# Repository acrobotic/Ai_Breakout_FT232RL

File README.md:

Overview
---
This repository includes the Eagle design files (schematics and layout) for our [FT232RL Brekout Board][1]. The FT232RL is a 
popular Integrated Circuit (IC) that provides a single-chip USB to asynchronous serial data (UART) transfer interface. This IC is
commonly known as the **FTDI chip** as it's manufactured by Future Technology Devices Internationa (FTDI).  

The FT232RL is extremely useful for sending data back and forth between a PC and a microcontroller (such as the ATMega328p 
that's used in the Arduino Uno R3). It can even be used to program a microcontroller whose boot section has been pre-loaded
with a bootloader (e.g., Optiboot).

For more info on how to use the FTDI and its use for data communication and microcontroller programming, please visit:
[http://learn.acrobotic.com/FTDI][2]

Product page
---
Please consider buying products from Acrobotic to help fund future Open-Source projects like this! We'll always put our best effort in every project, and release all our design files and code for you to use.

[Tutorials, technical details, and more information about this product can be found here: http://acrobotic.com/catalog/product/view/id/31][1]

License Information
---

All contents of this repository are licensed under a [Creative Commons Attribution-ShareAlike 3.0 Unported License](http://creativecommons.org/licenses/by-sa/3.0/).

[1]: http://acrobotic.com/catalog/product/view/id/31 "FT232RL Breakout Board"
[2]: http://learn.acrobotic.com/FTDI "Acrobotic FTDI Tutorial"

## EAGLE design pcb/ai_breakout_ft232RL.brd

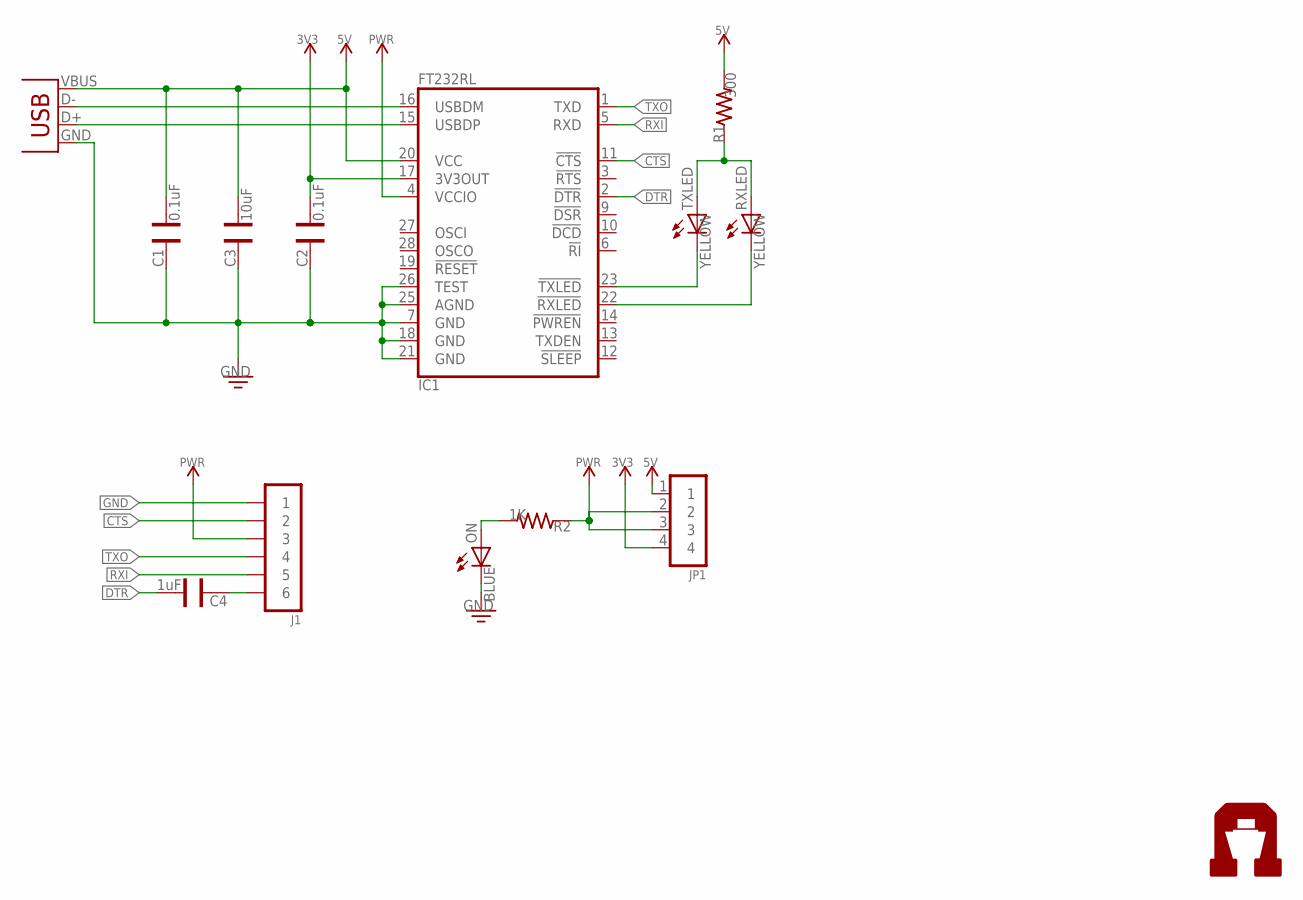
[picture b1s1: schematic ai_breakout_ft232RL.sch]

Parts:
C1, C2: 0.1uF; CAP-0603
C3: 10uF; CAP-0603
C4: 1uF; CAP-0603
IC1: FT2332RL; SSOP28-LD
J1: 1X06LONG; 1X06-LONG
JP1: 1X04NOSILK; 1X04-NOSILK
ON: BLUE; LED-0603
R1: 300; RES-0603
R2: 1K; RES-0603
RXLED: YELLOW; LED-0603
TXLED: YELLOW; LED-0603
U$3: AI-LOGOL; AI-LOGO-L
USB1: USBMICROB-TH; USB-MICROB-TH

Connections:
3V3: C2.1, IC1.17 (3V3OUT), JP1.4
5V: C1.1, C3.1, IC1.20 (VCC), JP1.1, R1.2, USB1.VBUS
CTS: IC1.11 (!CTS), J1.2
DTR: C4.1, IC1.2 (!DTR)
GND: C1.2, C2.2, C3.2, IC1.7 (GND), IC1.18 (GND), IC1.21 (GND), IC1.25 (AGND), IC1.26 (TEST), J1.1, ON.C, USB1.GND
unnamed: IC1.23 (!TXLED), TXLED.C
unnamed: IC1.22 (!RXLED), RXLED.C
unnamed: IC1.16 (USBDM), USB1.D-
unnamed: IC1.15 (USBDP), USB1.D+
unnamed: ON.A, R2.2
unnamed: R1.1, RXLED.A, TXLED.A
unnamed: C4.2, J1.6
PWR: IC1.4 (VCCIO), J1.3, JP1.2, JP1.3, R2.1
RXI: IC1.5 (RXD), J1.5
TXO: IC1.1 (TXD), J1.4

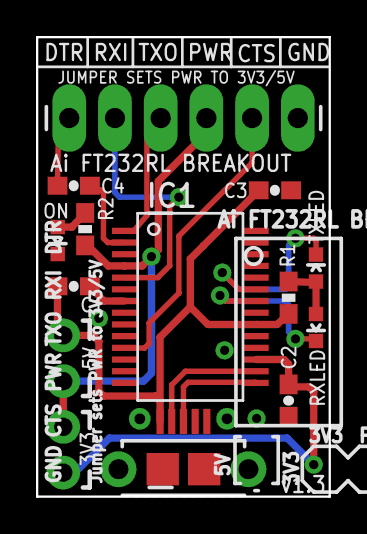
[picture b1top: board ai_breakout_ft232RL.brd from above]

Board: 2 copper layers, 16.3 x 25.5 mm, 14 parts (1 on the bottom side), 15 nets.

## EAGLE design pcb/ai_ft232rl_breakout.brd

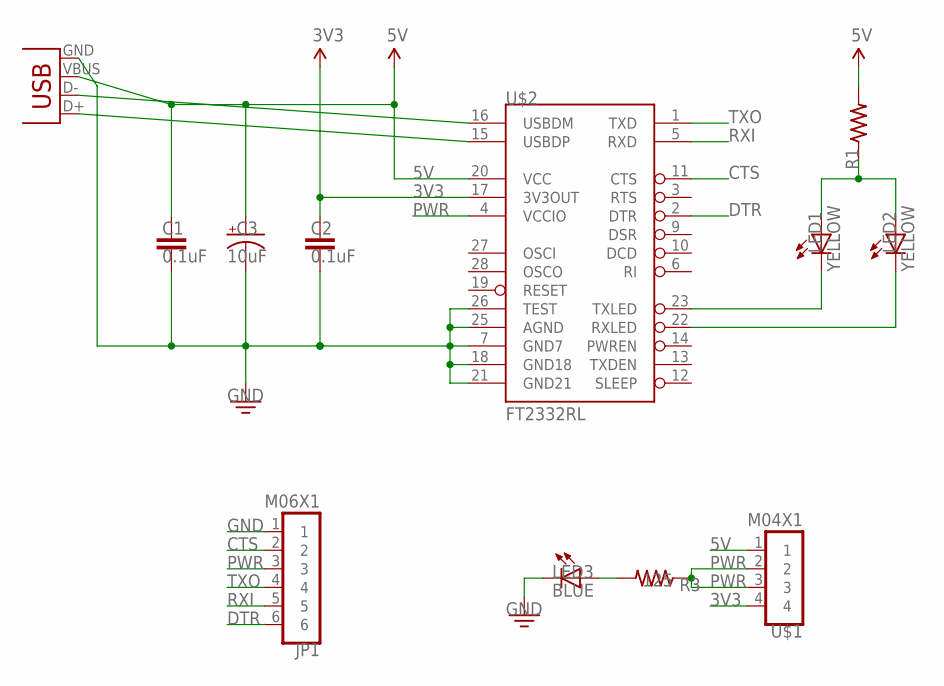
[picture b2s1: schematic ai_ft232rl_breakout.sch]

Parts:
C1, C2: 0.1uF; 0603-CAP
C3: 10uF; EIA3216
JP1: M06X1; 1X06-LONG
LED1, LED2: YELLOW; LED-0603
LED3: BLUE; LED-0603
R1: RES; 0603-RES
R3: 125; 0603-RES
U$1: M04X1; 1X04
U$2: FT2332RL; SSOP28-LD
USB1: USB-MICROB

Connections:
3V3: C2.1, U$1.4, U$2.17 (3V3OUT)
5V: C1.1, C3.A (+), R1.2, U$1.1, U$2.20 (VCC), USB1.VBUS
CTS: JP1.2, U$2.11 (CTS)
DTR: JP1.6, U$2.2 (DTR)
GND: C1.2, C2.2, C3.C (-), JP1.1, LED3.C, U$2.7 (GND7), U$2.18 (GND18), U$2.21 (GND21), U$2.25 (AGND), U$2.26 (TEST), USB1.GND
unnamed: LED1.C, U$2.23 (TXLED)
unnamed: LED2.C, U$2.22 (RXLED)
unnamed: U$2.16 (USBDM), USB1.D-
unnamed: U$2.15 (USBDP), USB1.D+
unnamed: LED1.A, LED2.A, R1.1
unnamed: LED3.A, R3.2
PWR: JP1.3, R3.1, U$1.2, U$1.3, U$2.4 (VCCIO)
RXI: JP1.5, U$2.5 (RXD)
TXO: JP1.4, U$2.1 (TXD)

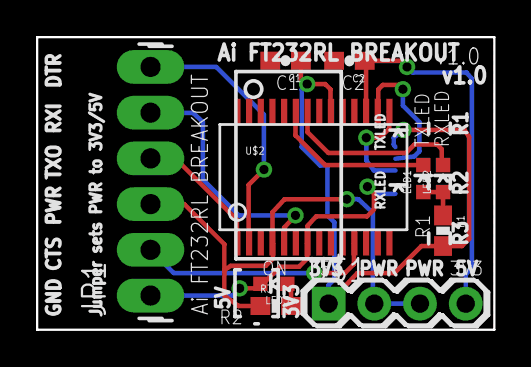
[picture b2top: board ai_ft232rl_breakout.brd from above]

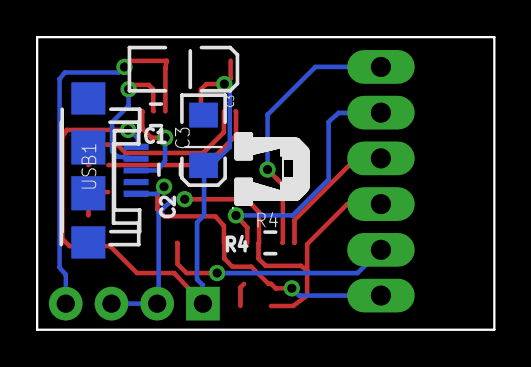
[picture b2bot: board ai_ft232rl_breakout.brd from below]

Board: 2 copper layers, 25.4 x 16.3 mm, 12 parts (2 on the bottom side), 14 nets.

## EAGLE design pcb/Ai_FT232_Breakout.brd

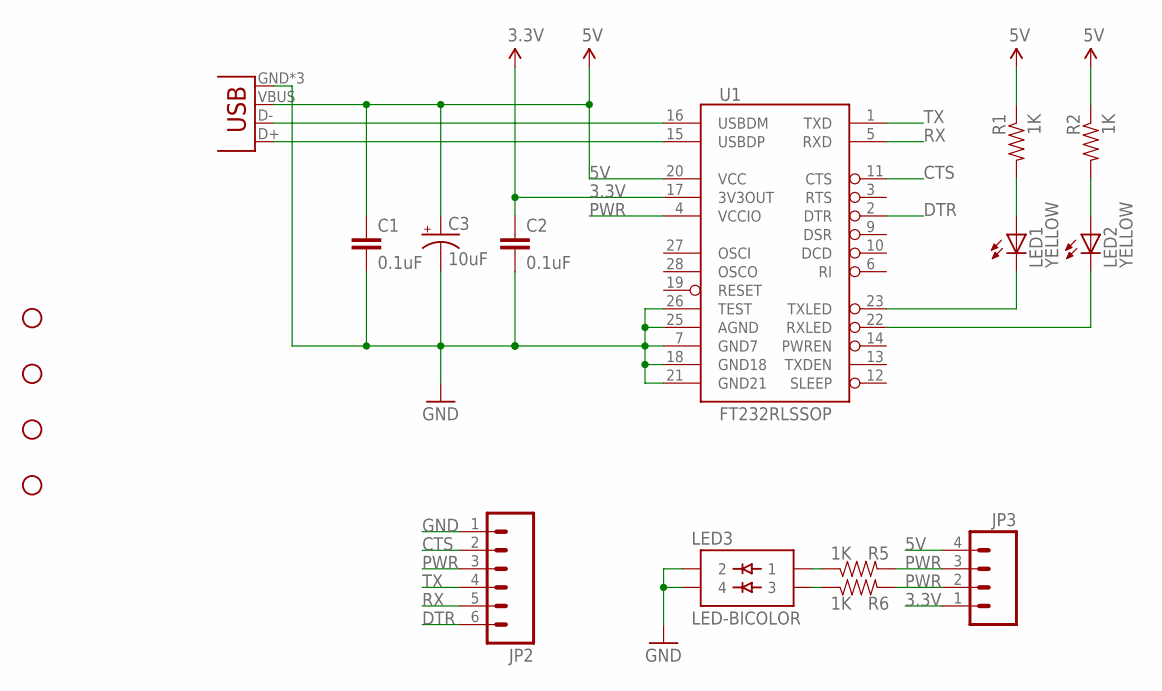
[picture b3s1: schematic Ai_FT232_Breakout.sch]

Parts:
C1, C2: 0.1uF; 0805
C3: 10uF; EIA3216-KIT
JP2: M06LONGPADS; 1X06_LONGPADS
JP3: M04PTH; 1X04
LED1, LED2: YELLOW; LED-0603
LED3: LED-BICOLOR; LED-BICOLOR-SMD
R1, R2, R5, R6: 1K; 0805
STANDOFF1, STANDOFF2, STANDOFF3, STANDOFF4: STAND-OFF
U1: FT232RLSSOP; SSOP28DB
USB: USB-MICROB

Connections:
3.3V: C2.1, JP3.1, U1.17 (3V3OUT)
5V: C1.1, C3.A (+), JP3.4, R1.1, R2.1, U1.20 (VCC), USB.VBUS
CTS: JP2.2, U1.11 (CTS)
DTR: JP2.6, U1.2 (DTR)
GND: C1.2, C2.2, C3.C (-), JP2.1, LED3.2 (4), LED3.3 (2), U1.7 (GND7), U1.18 (GND18), U1.21 (GND21), U1.25 (AGND), U1.26 (TEST), USB.GND, USB.MT1 (GND), USB.MT2 (GND)
unnamed: LED1.C, U1.23 (TXLED)
unnamed: LED2.C, U1.22 (RXLED)
unnamed: U1.16 (USBDM), USB.D-
unnamed: U1.15 (USBDP), USB.D+
unnamed: LED2.A, R2.2
unnamed: LED1.A, R1.2
unnamed: LED3.1, R5.1
unnamed: JP3.3, R5.2
unnamed: LED3.4 (3), R6.1
PWR: JP2.3, JP3.2, R6.2, U1.4 (VCCIO)
RX: JP2.5, U1.5 (RXD)
TX: JP2.4, U1.1 (TXD)

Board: 2 copper layers, 18 parts (0 on the bottom side), 17 nets, no tracks yet.

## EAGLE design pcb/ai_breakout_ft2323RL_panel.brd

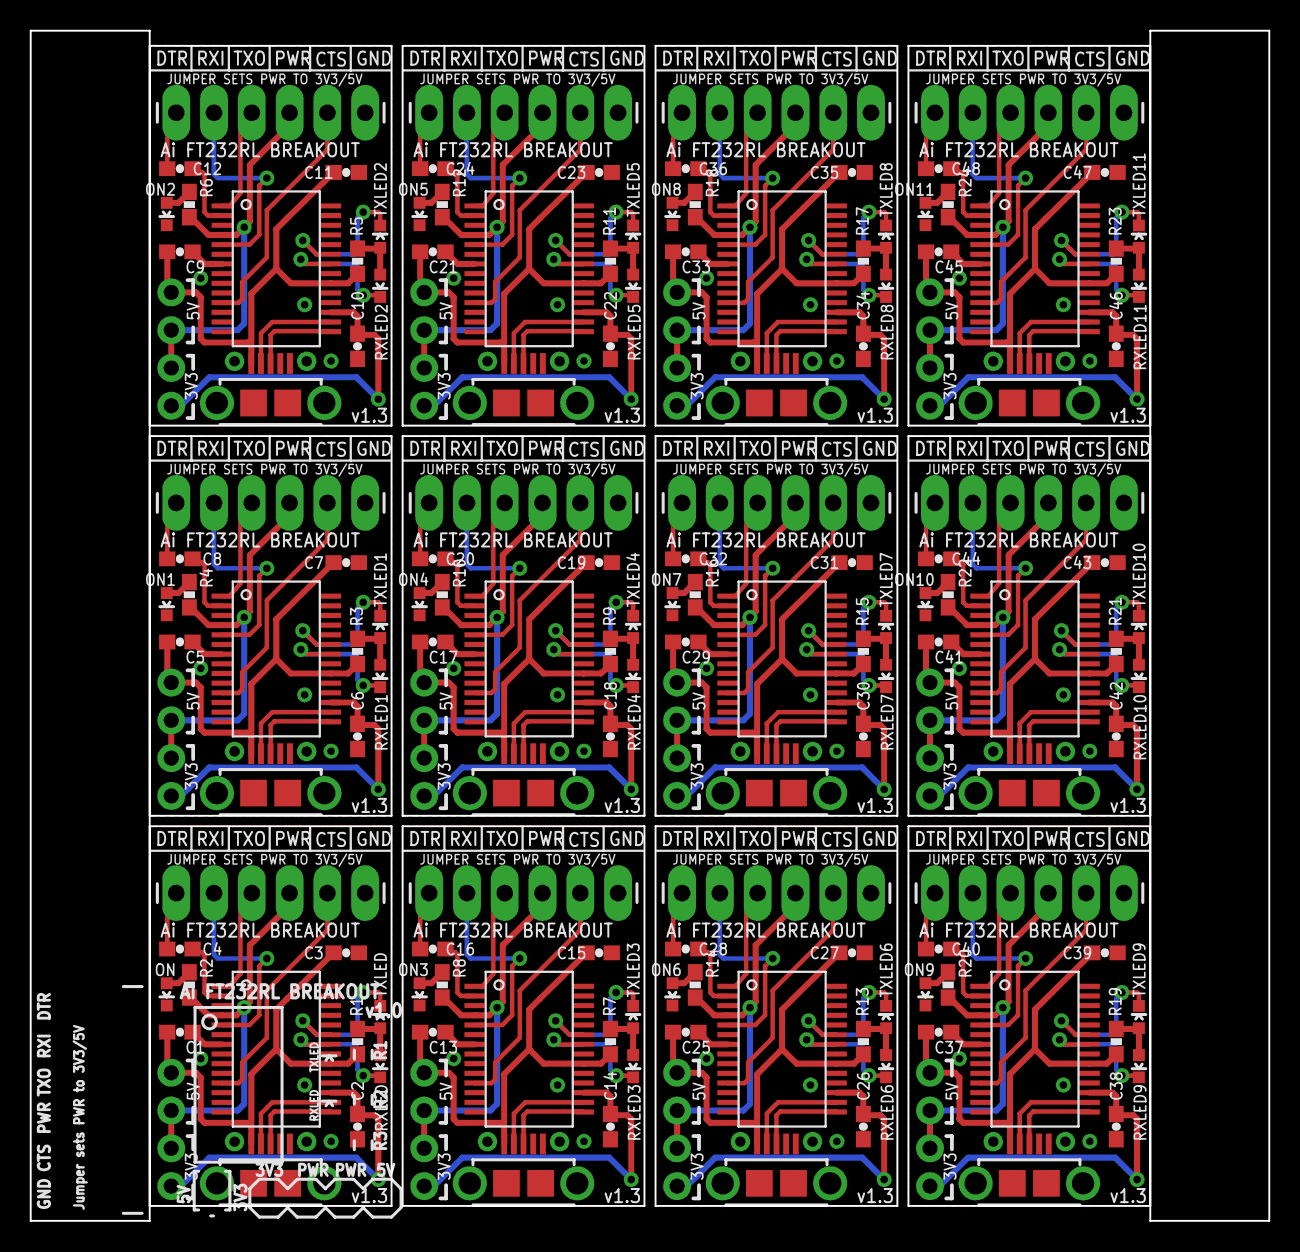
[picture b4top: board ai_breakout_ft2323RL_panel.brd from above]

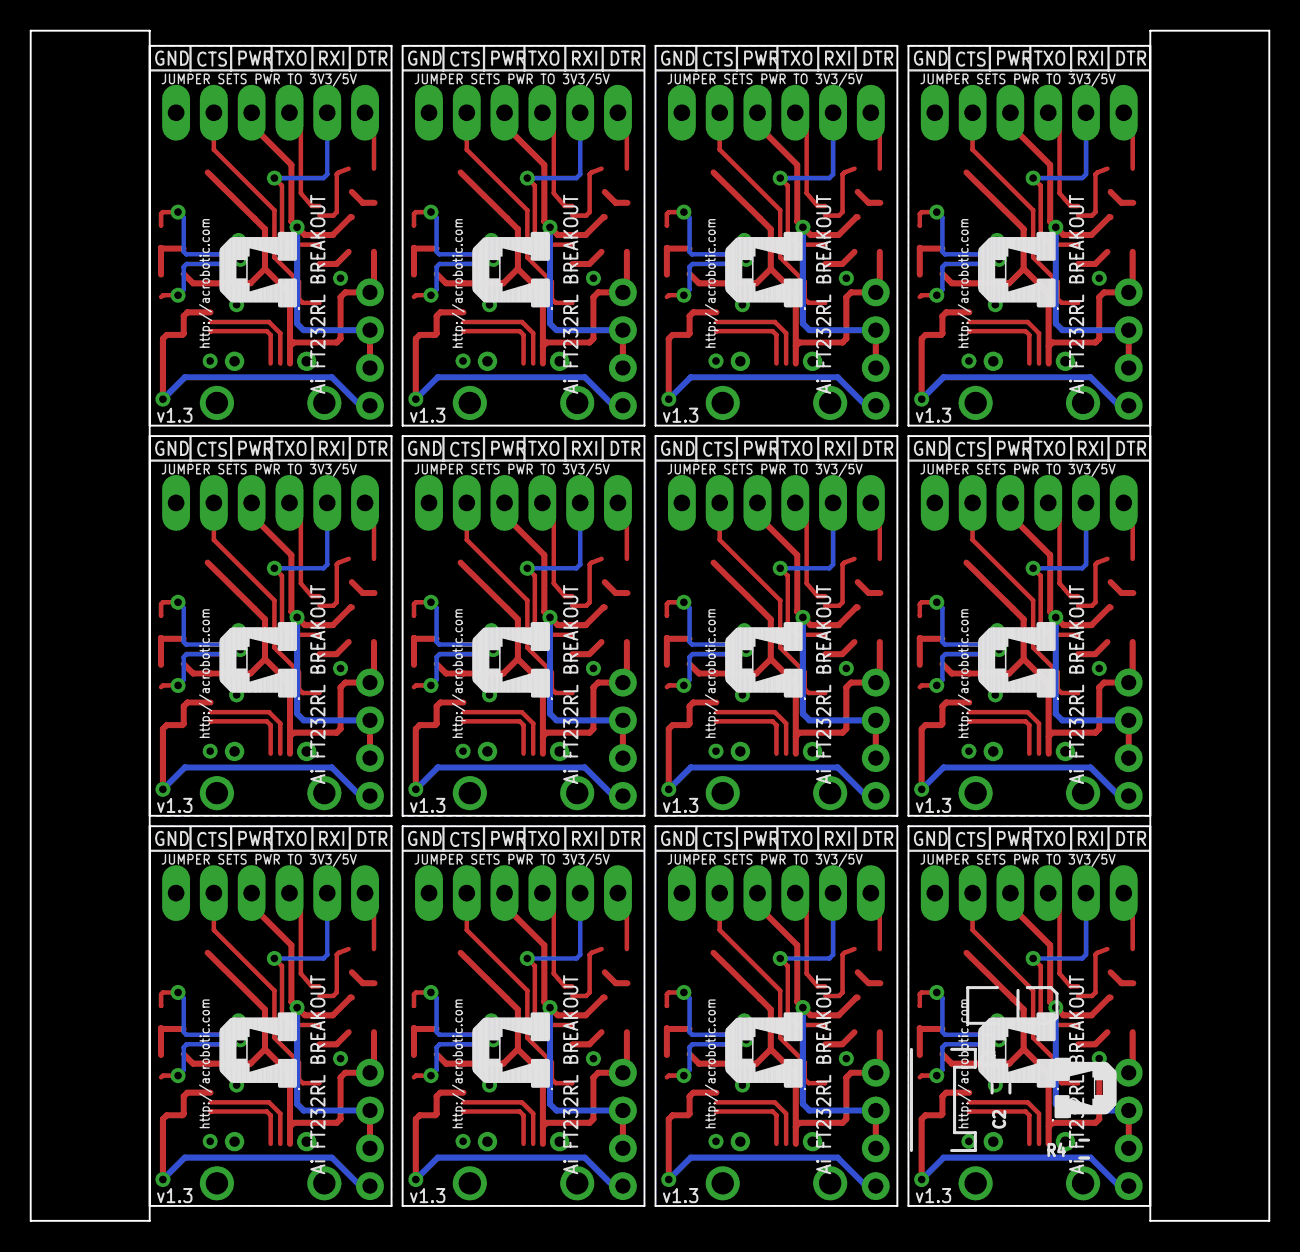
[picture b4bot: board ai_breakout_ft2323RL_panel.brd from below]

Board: 2 copper layers, 83.3 x 80.0 mm, 168 parts (12 on the bottom side), 180 nets.

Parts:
C1, C2, C5, C6, C9, C10, C13, C14, C17, C18, C21, C22, C25, C26, C29, C30, C33, C34, C37, C38, C41, C42, C45, C46: 0.1uF; CAP-0603
C3, C7, C11, C15, C19, C23, C27, C31, C35, C39, C43, C47: 10uF; CAP-0603
C4, C8, C12, C16, C20, C24, C28, C32, C36, C40, C44, C48: 1uF; CAP-0603
IC1, IC2, IC3, IC4, IC5, IC6, IC7, IC8, IC9, IC10, IC11, IC12: FT2332RL; SSOP28-LD
J1, J2, J3, J4, J5, J6, J7, J8, J9, J10, J11, J12: 1X06LONG; 1X06-LONG
JP1, JP2, JP3, JP4, JP5, JP6, JP7, JP8, JP9, JP10, JP11, JP12: 1X04NOSILK; 1X04-NOSILK
ON, ON1, ON2, ON3, ON4, ON5, ON6, ON7, ON8, ON9, ON10, ON11: BLUE; LED-0603
R1, R3, R5, R7, R9, R11, R13, R15, R17, R19, R21, R23: 300; RES-0603
R2, R4, R6, R8, R10, R12, R14, R16, R18, R20, R22, R24: 1K; RES-0603
RXLED, RXLED1, RXLED2, RXLED3, RXLED4, RXLED5, RXLED6, RXLED7, RXLED8, RXLED9, RXLED10, RXLED11: YELLOW; LED-0603
TXLED, TXLED1, TXLED2, TXLED3, TXLED4, TXLED5, TXLED6, TXLED7, TXLED8, TXLED9, TXLED10, TXLED11: YELLOW; LED-0603
U$1, U$2, U$3, U$4, U$5, U$6, U$7, U$8, U$9, U$10, U$11, U$12: AI-LOGOL; AI-LOGO-L
USB1, USB2, USB3, USB4, USB5, USB6, USB7, USB8, USB9, USB10, USB11, USB12: USBMICROB-TH; USB-MICROB-TH

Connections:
3V1: C6.1, IC2.17, JP2.4
3V2: C10.1, IC3.17, JP3.4
3V3: C2.1, IC1.17, JP1.4
3V4: C14.1, IC4.17, JP4.4
3V5: C18.1, IC5.17, JP5.4
3V6: C22.1, IC6.17, JP6.4
3V7: C26.1, IC7.17, JP7.4
3V8: C30.1, IC8.17, JP8.4
3V9: C34.1, IC9.17, JP9.4
3V10: C38.1, IC10.17, JP10.4
3V11: C42.1, IC11.17, JP11.4
3V12: C46.1, IC12.17, JP12.4
5V: C1.1, C3.1, IC1.20, JP1.1, R1.2, USB1.VBUS
5V1: C5.1, C7.1, IC2.20, JP2.1, R3.2, USB2.VBUS
5V2: C9.1, C11.1, IC3.20, JP3.1, R5.2, USB3.VBUS
5V3: C13.1, C15.1, IC4.20, JP4.1, R7.2, USB4.VBUS
5V4: C17.1, C19.1, IC5.20, JP5.1, R9.2, USB5.VBUS
5V5: C21.1, C23.1, IC6.20, JP6.1, R11.2, USB6.VBUS
5V6: C25.1, C27.1, IC7.20, JP7.1, R13.2, USB7.VBUS
5V7: C29.1, C31.1, IC8.20, JP8.1, R15.2, USB8.VBUS
5V8: C33.1, C35.1, IC9.20, JP9.1, R17.2, USB9.VBUS
5V9: C37.1, C39.1, IC10.20, JP10.1, R19.2, USB10.VBUS
5V10: C41.1, C43.1, IC11.20, JP11.1, R21.2, USB11.VBUS
5V11: C45.1, C47.1, IC12.20, JP12.1, R23.2, USB12.VBUS
CTS: IC1.11, J1.2
CTS1: IC2.11, J2.2
CTS2: IC3.11, J3.2
CTS3: IC4.11, J4.2
CTS4: IC5.11, J5.2
CTS5: IC6.11, J6.2
CTS6: IC7.11, J7.2
CTS7: IC8.11, J8.2
CTS8: IC9.11, J9.2
CTS9: IC10.11, J10.2
CTS10: IC11.11, J11.2
CTS11: IC12.11, J12.2
DTR: C4.1, IC1.2
DTR1: C8.1, IC2.2
DTR2: C12.1, IC3.2
DTR3: C16.1, IC4.2
DTR4: C20.1, IC5.2
DTR5: C24.1, IC6.2
DTR6: C28.1, IC7.2
DTR7: C32.1, IC8.2
DTR8: C36.1, IC9.2
DTR9: C40.1, IC10.2
DTR10: C44.1, IC11.2
DTR11: C48.1, IC12.2
GND: C1.2, C2.2, C3.2, IC1.7, IC1.18, IC1.21, IC1.25, IC1.26, J1.1, ON.C, USB1.GND
GND1: C5.2, C6.2, C7.2, IC2.7, IC2.18, IC2.21, IC2.25, IC2.26, J2.1, ON1.C, USB2.GND
GND2: C9.2, C10.2, C11.2, IC3.7, IC3.18, IC3.21, IC3.25, IC3.26, J3.1, ON2.C, USB3.GND
GND3: C13.2, C14.2, C15.2, IC4.7, IC4.18, IC4.21, IC4.25, IC4.26, J4.1, ON3.C, USB4.GND
GND4: C17.2, C18.2, C19.2, IC5.7, IC5.18, IC5.21, IC5.25, IC5.26, J5.1, ON4.C, USB5.GND
GND5: C21.2, C22.2, C23.2, IC6.7, IC6.18, IC6.21, IC6.25, IC6.26, J6.1, ON5.C, USB6.GND
GND6: C25.2, C26.2, C27.2, IC7.7, IC7.18, IC7.21, IC7.25, IC7.26, J7.1, ON6.C, USB7.GND
GND7: C29.2, C30.2, C31.2, IC8.7, IC8.18, IC8.21, IC8.25, IC8.26, J8.1, ON7.C, USB8.GND
GND8: C33.2, C34.2, C35.2, IC9.7, IC9.18, IC9.21, IC9.25, IC9.26, J9.1, ON8.C, USB9.GND
GND9: C37.2, C38.2, C39.2, IC10.7, IC10.18, IC10.21, IC10.25, IC10.26, J10.1, ON9.C, USB10.GND
GND10: C41.2, C42.2, C43.2, IC11.7, IC11.18, IC11.21, IC11.25, IC11.26, J11.1, ON10.C, USB11.GND
GND11: C45.2, C46.2, C47.2, IC12.7, IC12.18, IC12.21, IC12.25, IC12.26, J12.1, ON11.C, USB12.GND
unnamed: IC1.23, TXLED.C
unnamed: IC1.22, RXLED.C
unnamed: IC1.16, USB1.D-
unnamed: IC1.15, USB1.D+
unnamed: ON.A, R2.2
unnamed: R1.1, RXLED.A, TXLED.A
unnamed: C4.2, J1.6
unnamed: IC2.16, USB2.D-
unnamed: IC2.15, USB2.D+
unnamed: R3.1, RXLED1.A, TXLED1.A
unnamed: ON1.A, R4.2
unnamed: IC2.23, TXLED1.C
unnamed: IC2.22, RXLED1.C
unnamed: C8.2, J2.6
unnamed: IC3.16, USB3.D-
unnamed: IC3.15, USB3.D+
unnamed: R5.1, RXLED2.A, TXLED2.A
unnamed: ON2.A, R6.2
unnamed: IC3.23, TXLED2.C
unnamed: IC3.22, RXLED2.C
unnamed: C12.2, J3.6
unnamed: IC4.16, USB4.D-
unnamed: IC4.15, USB4.D+
unnamed: R7.1, RXLED3.A, TXLED3.A
unnamed: ON3.A, R8.2
unnamed: IC4.23, TXLED3.C
unnamed: IC4.22, RXLED3.C
unnamed: C16.2, J4.6
unnamed: IC5.16, USB5.D-
unnamed: IC5.15, USB5.D+
unnamed: R9.1, RXLED4.A, TXLED4.A
unnamed: ON4.A, R10.2
unnamed: IC5.23, TXLED4.C
unnamed: IC5.22, RXLED4.C
unnamed: C20.2, J5.6
unnamed: IC6.16, USB6.D-
unnamed: IC6.15, USB6.D+
unnamed: R11.1, RXLED5.A, TXLED5.A
unnamed: ON5.A, R12.2
unnamed: IC6.23, TXLED5.C
unnamed: IC6.22, RXLED5.C
unnamed: C24.2, J6.6
unnamed: IC7.16, USB7.D-
unnamed: IC7.15, USB7.D+
unnamed: R13.1, RXLED6.A, TXLED6.A
unnamed: ON6.A, R14.2
unnamed: IC7.23, TXLED6.C
unnamed: IC7.22, RXLED6.C
unnamed: C28.2, J7.6
unnamed: IC8.16, USB8.D-
unnamed: IC8.15, USB8.D+
unnamed: R15.1, RXLED7.A, TXLED7.A
unnamed: ON7.A, R16.2
unnamed: IC8.23, TXLED7.C
unnamed: IC8.22, RXLED7.C
unnamed: C32.2, J8.6
unnamed: IC9.16, USB9.D-
unnamed: IC9.15, USB9.D+
unnamed: R17.1, RXLED8.A, TXLED8.A
unnamed: ON8.A, R18.2
unnamed: IC9.23, TXLED8.C
unnamed: IC9.22, RXLED8.C
unnamed: C36.2, J9.6
unnamed: IC10.16, USB10.D-
unnamed: IC10.15, USB10.D+
unnamed: R19.1, RXLED9.A, TXLED9.A
unnamed: ON9.A, R20.2
unnamed: IC10.23, TXLED9.C
unnamed: IC10.22, RXLED9.C
unnamed: C40.2, J10.6
unnamed: IC11.16, USB11.D-
unnamed: IC11.15, USB11.D+
unnamed: R21.1, RXLED10.A, TXLED10.A
unnamed: ON10.A, R22.2
unnamed: IC11.23, TXLED10.C
unnamed: IC11.22, RXLED10.C
unnamed: C44.2, J11.6
unnamed: IC12.16, USB12.D-
unnamed: IC12.15, USB12.D+
unnamed: R23.1, RXLED11.A, TXLED11.A
unnamed: ON11.A, R24.2
unnamed: IC12.23, TXLED11.C
unnamed: IC12.22, RXLED11.C
unnamed: C48.2, J12.6
PWR: IC1.4, J1.3, JP1.2, JP1.3, R2.1
PWR1: IC2.4, J2.3, JP2.2, JP2.3, R4.1
PWR2: IC3.4, J3.3, JP3.2, JP3.3, R6.1
PWR3: IC4.4, J4.3, JP4.2, JP4.3, R8.1
PWR4: IC5.4, J5.3, JP5.2, JP5.3, R10.1
PWR5: IC6.4, J6.3, JP6.2, JP6.3, R12.1
PWR6: IC7.4, J7.3, JP7.2, JP7.3, R14.1
PWR7: IC8.4, J8.3, JP8.2, JP8.3, R16.1
PWR8: IC9.4, J9.3, JP9.2, JP9.3, R18.1
PWR9: IC10.4, J10.3, JP10.2, JP10.3, R20.1
PWR10: IC11.4, J11.3, JP11.2, JP11.3, R22.1
PWR11: IC12.4, J12.3, JP12.2, JP12.3, R24.1
RXI: IC1.5, J1.5
RXI1: IC2.5, J2.5
RXI2: IC3.5, J3.5
RXI3: IC4.5, J4.5
RXI4: IC5.5, J5.5
RXI5: IC6.5, J6.5
RXI6: IC7.5, J7.5
RXI7: IC8.5, J8.5
RXI8: IC9.5, J9.5
RXI9: IC10.5, J10.5
RXI10: IC11.5, J11.5
RXI11: IC12.5, J12.5
TXO: IC1.1, J1.4
TXO1: IC2.1, J2.4
TXO2: IC3.1, J3.4
TXO3: IC4.1, J4.4
TXO4: IC5.1, J5.4
TXO5: IC6.1, J6.4
TXO6: IC7.1, J7.4
TXO7: IC8.1, J8.4
TXO8: IC9.1, J9.4
TXO9: IC10.1, J10.4
TXO10: IC11.1, J11.4
TXO11: IC12.1, J12.4

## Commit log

2013-07-17 first commit.
2013-07-18 version 1.0 of the design files.
2013-07-18 removing unwanted files.
2013-07-18 changed the size of the board's png.
2013-07-18 aligned board to origin.
2013-07-22 re-routed manually, and changed components to use the Ai Eagle libraries.
2013-07-25 changed pcb edge width
2013-07-25 renaming files.
2013-07-25 deleting old (renamed) files.
2013-07-26 Small fixup in schematic
2013-10-05 Revision 1.1
2013-10-05 Finalized BOM
2013-10-05 Final version 1.1
2013-10-05 First commit for pages branch.
2013-10-05 Minor changes to README file.
2013-10-05 Fixed silkscreen typo
2013-10-11 Small changes in trace sizes, and silkscreen
2013-10-11 updating pdf file for schematic
2013-10-11 updating pdf file of schematics
2013-10-15 minor change on gerbers
2013-11-21 New revision and adding panelized version
2013-11-22 Updated BOM
2013-11-22 updating schematic pdf
2013-12-15 changed casing of filename
2013-12-15 fixed typo in filenames
2013-12-15 fixed typo in filename
2014-02-06 updated the micro-b connector and designed a new panelized version
2014-02-07 deleting old files named using lowercase rl
2014-02-07 updating schematic and its filename
2014-02-07 deleting old files named using 2323 instead of 232
2014-02-07 deleting old files named using RL instead of rl
2014-09-05 updating libraries
2014-09-05 small update to BOM

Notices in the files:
parts and their libraries:
SparkFun-Electromechanical: Licensing: CC v3.0 Share-Alike You are welcome to use this library for commercial purposes.
